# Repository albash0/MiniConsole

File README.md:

# MiniConsole

**A pocket game console built across embedded software, custom electronics, and physical design.**

*Built hardware: the earlier OLED handheld above and the color TFT handheld below. Photograph provided by the project author.*

An ESP32-S3 handheld with six buttons, OLED and color TFT versions, custom carrier PCBs, and a printable enclosure. The library combines arcade games, puzzles, an original traffic-planning implementation, adapted Doom support, and wireless play between two consoles.

A project by [albash0](https://github.com/albash0), a first-year ASEN and CTD student at CU Boulder.

[Engineering notes](docs/ENGINEERING.md) · [Hardware and case files](#hardware) · [Build instructions](docs/BUILD.md) · [Controls](docs/USER_GUIDE.md) · [Validation](VALIDATION.md)

## About the project

MiniConsole began with Snake and portrait Tetris on a 128 × 64 OLED. Extending it to a 240 × 135 color display introduced new memory, rendering, input, and mechanical-fit constraints. Wireless co-op added a second device whose state had to remain consistent with the first.

### From prototype to finished handheld

| Electronics iteration | Enclosure fit test | Assembled generations |
| --- | --- | --- |
|  |  |  |
| OLED protoboard prototype at the top; custom TFT PCB below. | A printed front shell brings together the display opening, button guides, fasteners, and handheld form. | Color TFT version in front; earlier OLED version behind. |

These build photographs show the progression from electronics integration to enclosure fitting and assembled devices. [Photo provenance and metadata handling](docs/media/photos/README.md).

### My project work

| Area | Work in this project | Source and evidence |
| --- | --- | --- |
| Firmware and interaction | Game launcher, six-button navigation, display profiles, themes, sound, and persistent checkpoints | [Main firmware](MiniConsole/MiniConsole.ino), [checkpoint implementation](MiniConsole/SuspendSave.h), [user guide](docs/USER_GUIDE.md) |
| Games and networking | Micro Motorways traffic simulation; Pocket Partners rooms and host-authoritative co-op; Block Battle Tetris mode | [Traffic model](MiniConsole/MotorwaysGame.h), [co-op implementation](MiniConsole/PartnersLink.h), [protocol tests](MiniConsole/tests/partners_test.cpp) |
| Hardware integration | OLED and TFT carrier-board designs, component/pin mapping, and fabrication outputs | [OLED carrier](MiniConsole/PCB/), [TFT carrier](MiniConsole/PCB-TFT114/) |
| Mechanical design | Screen/PCB fit, keyed button guides, and printable plain rear-shell choices | [STEP/STL parts and assembly constraints](hardware/case/) |
| Validation and tooling | Automated game/controller/rendering tests, firmware builds, and documented hardware bring-up | [Test runner](MiniConsole/tests/run_tests.sh), [validation report](VALIDATION.md) |

**Upstream work:** Doom support adapts DIABLITO, descended from RP2040 Doom and Chocolate Doom. The original game engine and assets have their own authors and licenses. My project integrates that engine with the S3, displays, controls, launcher, and saves. The complete adapted source is included under [DiablitoOLED](libraries/DiablitoOLED/); see [credits and licenses](THIRD_PARTY.md).

### Engineering decisions

- **Share game rules across displays:** keep common state and checkpoint formats while allowing native color rendering where it improves the interface.
- **Budget memory explicitly:** a single full-panel RGB565 buffer is 64,800 bytes; the TFT backend attempts PSRAM allocation first.
- **Use one authority for co-op physics:** the host owns the world state; clients send inputs and receive snapshots, with stalls and disconnects handled explicitly.
- **Treat fit as part of the system:** screen height, switch travel, retaining flanges, and battery clearance constrain the enclosure together.

[Read the decisions, source links, regression example, and next measurements →](docs/ENGINEERING.md)

### Status and validation

| Check | Evidence and limits |
| --- | --- |
| Automated tests | **30 host suites per display profile** pass with address/undefined-behavior sanitizers. [GitHub Actions](https://github.com/albash0/MiniConsole/actions). |
| Firmware | OLED and TFT profiles compiled for the public source release. |
| Physical devices | The [build photographs](#from-prototype-to-finished-handheld) show OLED/TFT assemblies and enclosure iteration. Development records document bring-up and nearby two-console co-op/battle testing. The source release itself did not include a new device flash or gameplay run. |
| CAD and fabrication | Editable KiCad designs, BOMs, fabrication files, and individual case parts are supplied. Physical assembly tolerances still need checking. |
| Open measurements | Battery runtime, defined wireless range, and repeatable frame-time comparisons remain to be measured. |

Host tests stub the Doom engine; their success does not establish Doom runtime behavior on hardware. [Validation details](VALIDATION.md).

### Timeline

Dates below come from dated validation notes and source/CAD records; early dates identify the earliest retained files, rather than a reconstructed Git history.

| Date | Milestone |
| --- | --- |
| 2026-10-12 | Earliest retained Snake and Tetris game sources. |
| 2026-10-13 | Breakout, Invaders and ten-level Sokoban; pause/resume checkpoints; DIABLITO-based Doom integration on the OLED console. |
| 2026-10-14 | Custom OLED and 1.14-inch TFT carrier-board design records. |
| 2026-10-16 | Going Out mode: persistent drink counter, configurable goal, and three party games. |
| 2026-10-29 | Color TFT firmware validated on the assembled console, including Doom. |
| 2026-10-30 | Native TFT game presentation and appearance work. |
| 2026-11-05 | Shorter case top selected after a physical test print. |
| 2026-11-09 | Piezo sound, Tetris music, themes, independent music/background controls, and keyed case refinements. |
| 2026-11-10–11 | Micro Motorways: traffic simulation, roads, bridges, express links, endless growth, diagonal roads and junction balancing. |
| 2026-11-12 | Wireless Tetris Block Battle and ten-room Pocket Partners co-op, tested on two TFT consoles. |
| 2026-11-17 | Public source preparation, portable build instructions and privacy review. |

## Games and controls

| Snake | Micro Motorways | Pocket Partners |
| --- | --- | --- |
|  |  |  |

*Host-rendered frames from the firmware's TFT renderer, separate from the physical build photographs above.*

The main library includes **Snake, Tetris, Breakout, Invaders, Sokoban, Doom, Micro Motorways, and Pocket Partners**. Tetris also has a two-console Block Battle mode. Pocket Partners has ten cooperative platform-puzzle rooms, and Sokoban has ten original puzzles.

The TFT version adds native menus, selected native game renderers, themes, and color. Checkpoints, settings, and high scores persist across restarts. Wireless modes use ESP-NOW without a router. Optional Going Out mode includes a drink counter and three party games; it is documented with the [full controls](docs/USER_GUIDE.md).

## Hardware

| Version or part | Files |
| --- | --- |
| OLED carrier V1.7 | [KiCad, Gerbers, BOM and board notes](MiniConsole/PCB/) |
| 1.14-inch ST7789 TFT carrier V1.3 | [KiCad, Gerbers, BOM and board notes](MiniConsole/PCB-TFT114/) |
| Keyed TFT enclosure | [Individual STEP/STL fronts, plain rears and buttons](hardware/case/) |

Both carriers use an ESP32-S3 SuperMini, six buttons, and an optional GPIO4 piezo through 220 Ω. Read the [TFT battery wiring correction](MiniConsole/PCB-TFT114/wiring/README.md) before assembly. The enclosure notes cover the thicker rear's battery-clearance constraint.

## Build and test

[The build guide](docs/BUILD.md) covers dependencies, OLED/TFT selection, first installation, and the separate Doom shareware-data download. Commands below run from the repository root:

```sh
python3 MiniConsole/tools/build_doom.py --display oled
python3 MiniConsole/tools/build_doom.py --display tft
sh MiniConsole/tests/run_tests.sh
DISPLAY_PROFILE=tft sh MiniConsole/tests/run_tests.sh
```

## License and credits

Original software, documentation and design files: **GPL-2.0-or-later**, except retained third-party notices. See [LICENSE](LICENSE) and [THIRD_PARTY.md](THIRD_PARTY.md). DIABLITO, RP2040 Doom, Chocolate Doom, id Software, Adafruit and KiCad contributors retain their credits and licenses. Doom game data is licensed separately.

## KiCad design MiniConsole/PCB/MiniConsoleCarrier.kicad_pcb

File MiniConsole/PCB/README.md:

# MiniConsole OLED carrier V1.7

Open `MiniConsoleCarrier.kicad_pro` in KiCad 10. The checked schematic, routed PCB, local symbols/footprints and unpacked manufacturing outputs are included. Use the native KiCad design as the authority; the EAGLE/Fusion interchange files may require copper-polygon regeneration and DRC after import.

The carrier is 70.1 × 30.1 mm with a 65.9 × 26.1 mm case mounting pattern. This revision adds five rear test pads and moves Left/Right inward 0.50 mm each. The expansion header is above Up. VCC and logic are 3.3 V. See `documentation/BOM.csv`, `manufacturing/`, and the retained geometry/check reports in `documentation/`.

Pin assignments and display setup are in [the user guide](../../docs/USER_GUIDE.md). The TFT carrier's firmware A/B mapping follows the physical assembled console and differs from older board labels. On the TFT board, read [the battery wiring correction](../PCB-TFT114/wiring/README.md) before wiring the battery. The PCB reference and copper pin numbers take precedence over conflicting silkscreen.

The original hardware records report no DRC/ERC violations with the configured rules. Those are historical CAD checks, not a new hardware test. Confirm module dimensions, polarity, clearances and the fabrication house's rules before manufacturing. Component models are nominal fit references; their original notices are under `3dmodels/`.

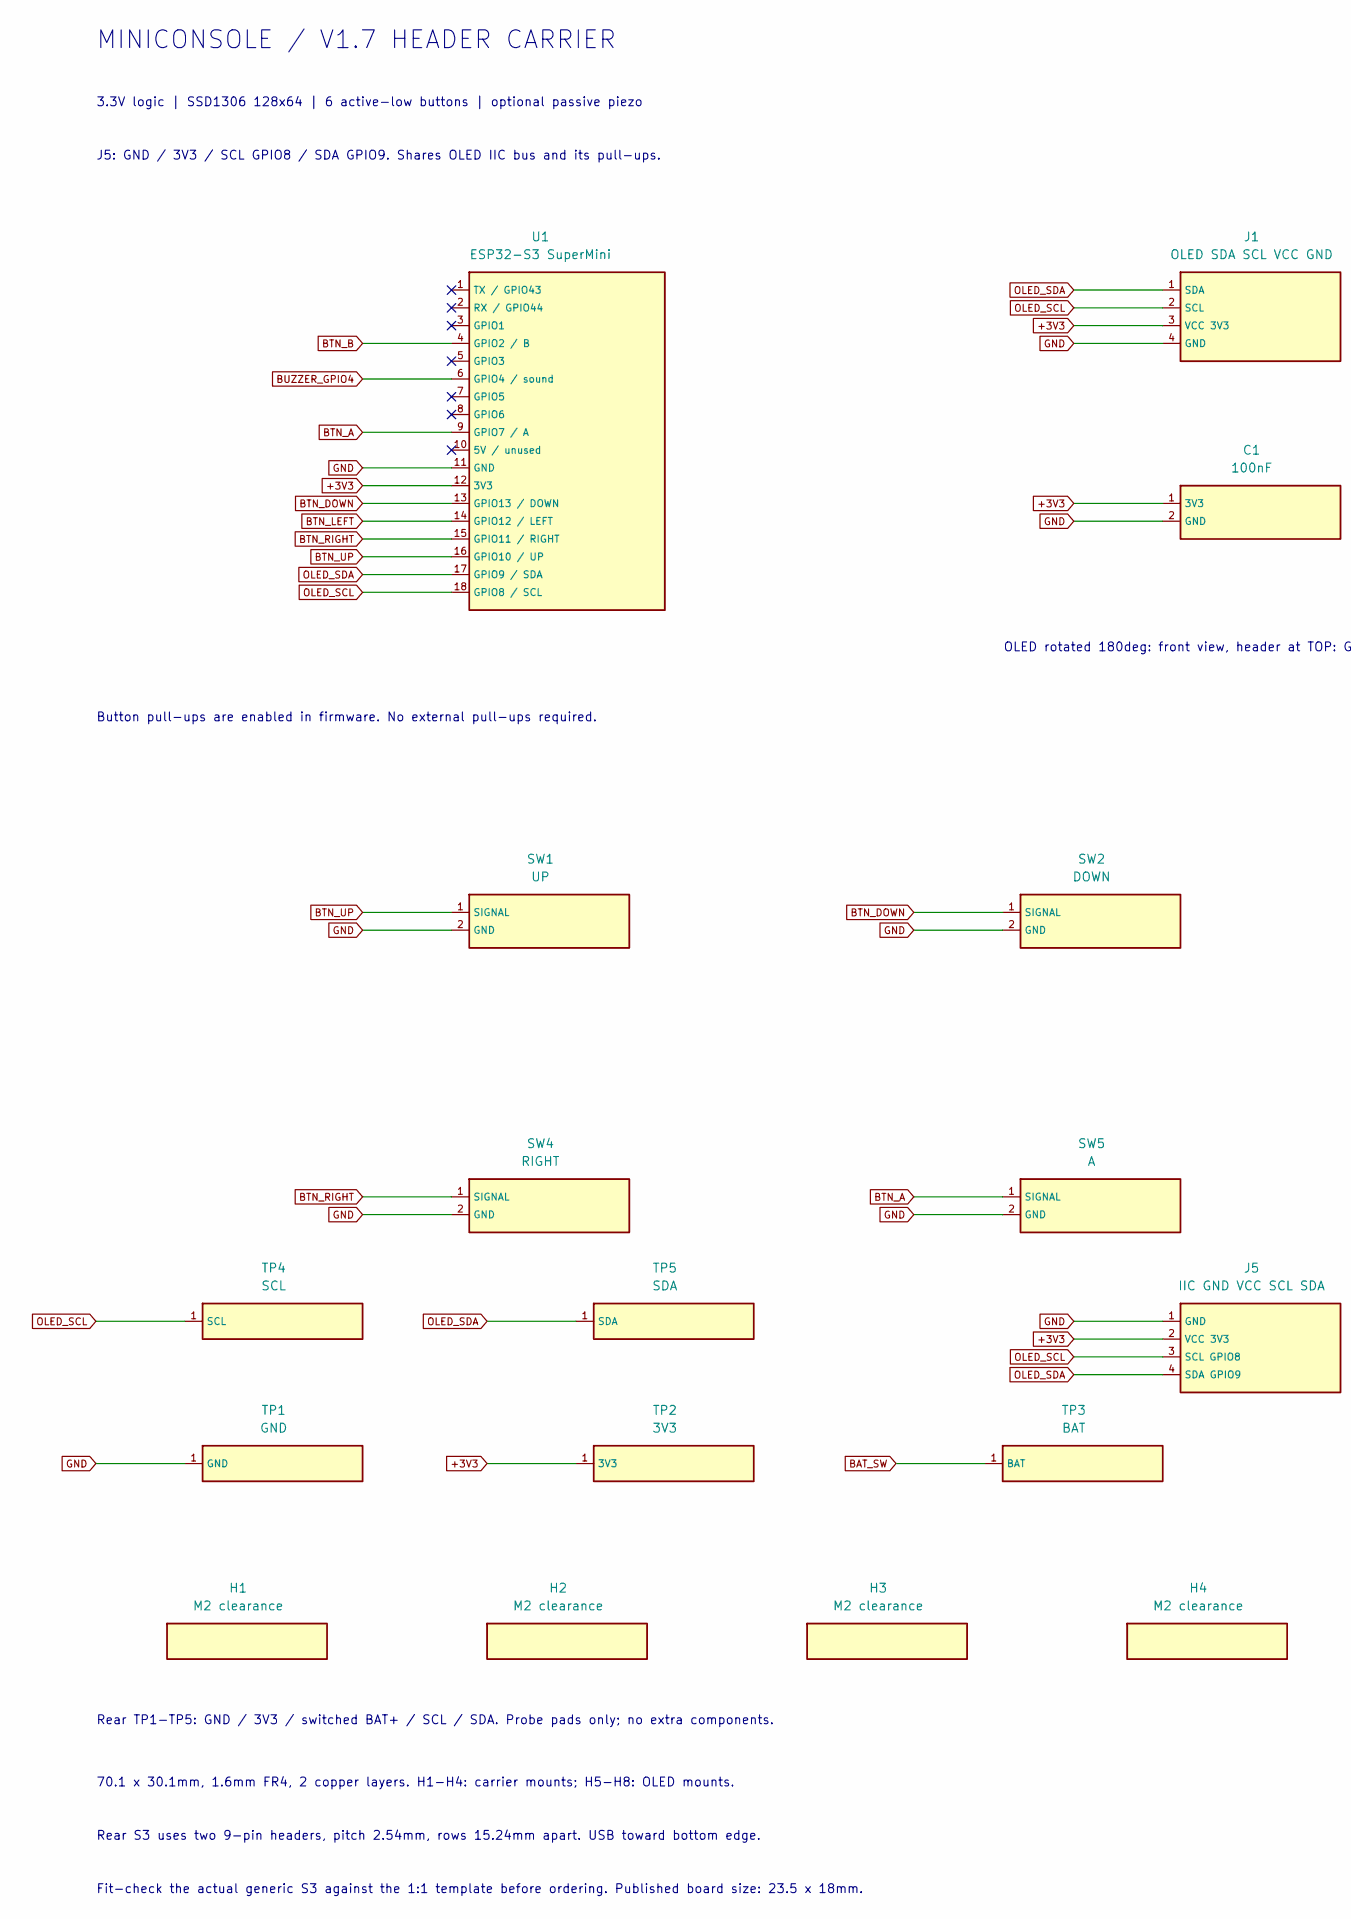
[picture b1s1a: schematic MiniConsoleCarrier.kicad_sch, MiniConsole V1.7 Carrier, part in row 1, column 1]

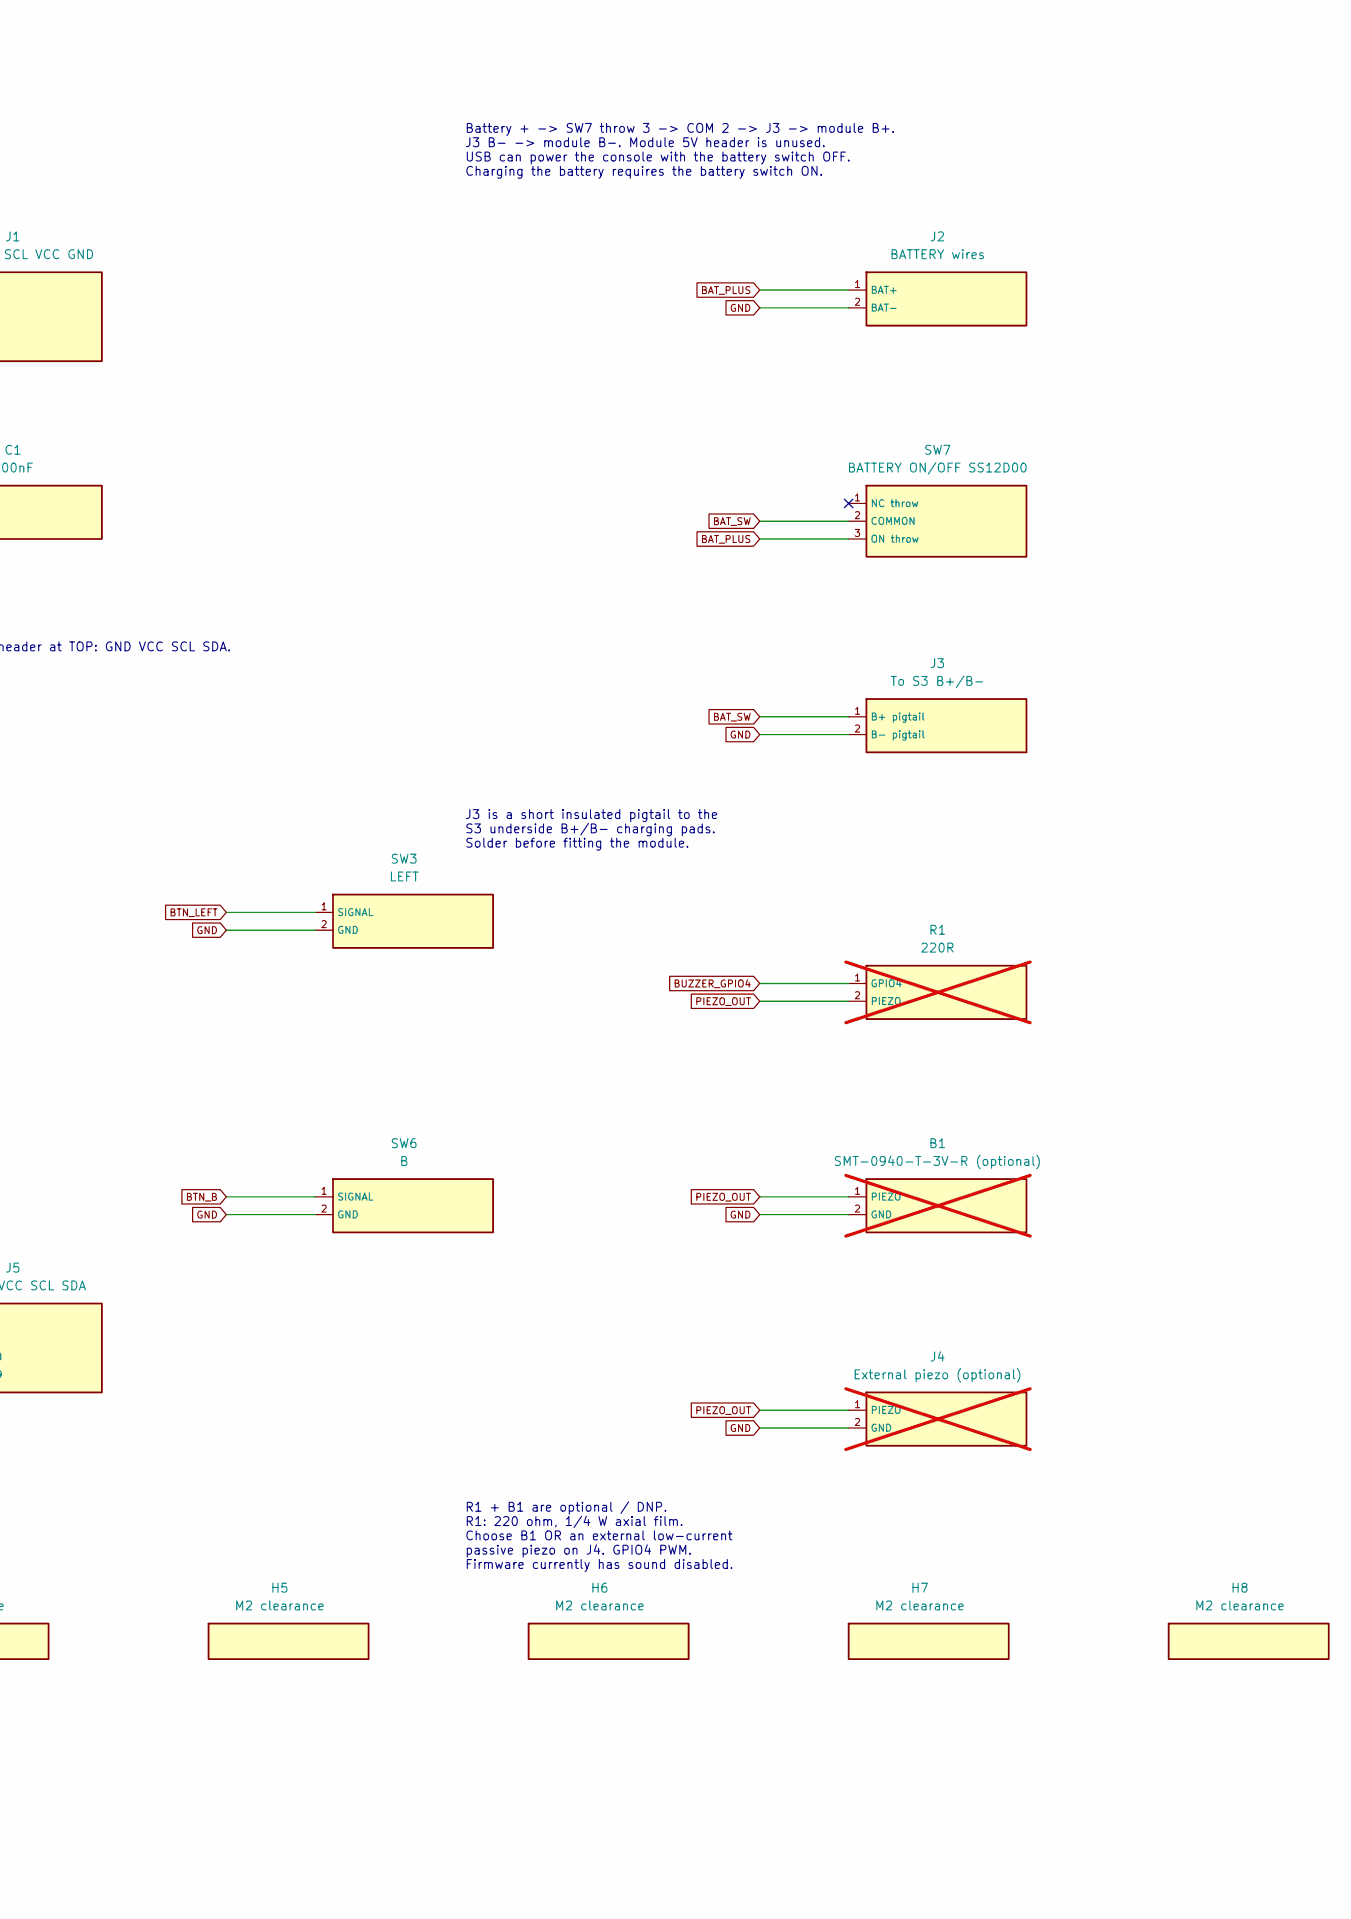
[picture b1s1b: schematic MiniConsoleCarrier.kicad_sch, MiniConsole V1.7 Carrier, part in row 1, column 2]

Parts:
B1: SMT-0940-T-3V-R (optional); Piezo_PUI_SMT0940_180; not fitted
C1: 100nF; C_0603_180
H1, H2, H3, H4, H5, H6, H7, H8: M2 clearance; Mount_M2
J1: OLED SDA SCL VCC GND; OLED_1x04
J2: BATTERY wires; Wire_2x_2.54_Reverse
J3: To S3 B+/B-; Wire_2x_2.54
J4: External piezo (optional); Wire_2x_2.54_Reverse; not fitted
J5: IIC GND VCC SCL SDA; IIC_1x04
R1: 220R; R_Axial_DIN0207_P7.62_220R; not fitted
SW1: UP; SW_6mm
SW2: DOWN; SW_6mm
SW3: LEFT; SW_6mm_90
SW4: RIGHT; SW_6mm_90
SW5: A; SW_6mm
SW6: B; SW_6mm
SW7: BATTERY ON/OFF SS12D00; SS12D00_LeftEdge_3pin
TP1: GND; TestPoint_D1p5_Rear
TP2: 3V3; TestPoint_D1p5_Rear
TP3: BAT; TestPoint_D1p5_Rear
TP4: SCL; TestPoint_D1p5_Rear
TP5: SDA; TestPoint_D1p5_Rear
U1: ESP32-S3 SuperMini; S3_Rear_USB_Down_2x09

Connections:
+3V3: C1.1 (3V3), J1.3 (VCC 3V3), J5.2 (VCC 3V3), TP2.1, U1.12 (3V3)
BAT_PLUS: J2.1 (BAT+), SW7.3 (ON throw)
BAT_SW: J3.1 (B+ pigtail), SW7.2 (COMMON), TP3.1
BTN_A: SW5.1 (SIGNAL), U1.9 (GPIO7 / A)
BTN_B: SW6.1 (SIGNAL), U1.4 (GPIO2 / B)
BTN_DOWN: SW2.1 (SIGNAL), U1.13 (GPIO13 / DOWN)
BTN_LEFT: SW3.1 (SIGNAL), U1.14 (GPIO12 / LEFT)
BTN_RIGHT: SW4.1 (SIGNAL), U1.15 (GPIO11 / RIGHT)
BTN_UP: SW1.1 (SIGNAL), U1.16 (GPIO10 / UP)
BUZZER_GPIO4: R1.1 (GPIO4), U1.6 (GPIO4 / sound)
GND: B1.2 (GND), C1.2 (GND), J1.4 (GND), J2.2 (BAT-), J3.2 (B- pigtail), J4.2 (GND), J5.1 (GND), SW1.2 (GND), SW2.2 (GND), SW3.2 (GND), SW4.2 (GND), SW5.2 (GND), SW6.2 (GND), TP1.1, U1.11 (GND)
OLED_SCL: J1.2 (SCL), J5.3 (SCL GPIO8), TP4.1, U1.18 (GPIO8 / SCL)
OLED_SDA: J1.1 (SDA), J5.4 (SDA GPIO9), TP5.1, U1.17 (GPIO9 / SDA)
PIEZO_OUT: B1.1 (PIEZO), J4.1 (PIEZO), R1.2 (PIEZO)

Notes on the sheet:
MINICONSOLE / V1.7 HEADER CARRIER
3.3V logic | SSD1306 128x64 | 6 active-low buttons | optional passive piezo
J5: GND / 3V3 / SCL GPIO8 / SDA GPIO9. Shares OLED IIC bus and its pull-ups.
Button pull-ups are enabled in firmware. No external pull-ups required.
OLED rotated 180deg: front view, header at TOP: GND VCC SCL SDA.
Battery + -> SW7 throw 3 -> COM 2 -> J3 -> module B+. J3 B- -> module B-. Module 5V header is unused. USB can power the console with the battery switch OFF. Charging the battery requires the battery switch ON.
J3 is a short insulated pigtail to the S3 underside B+/B- charging pads. Solder before fitting the module.
R1 + B1 are optional / DNP. R1: 220 ohm, 1/4 W axial film. Choose B1 OR an external low-current passive piezo on J4. GPIO4 PWM. Firmware currently has sound disabled.
Rear TP1-TP5: GND / 3V3 / switched BAT+ / SCL / SDA. Probe pads only; no extra components.
70.1 x 30.1mm, 1.6mm FR4, 2 copper layers. H1-H4: carrier mounts; H5-H8: OLED mounts.
Rear S3 uses two 9-pin headers, pitch 2.54mm, rows 15.24mm apart. USB toward bottom edge.
Fit-check the actual generic S3 against the 1:1 template before ordering. Published board size: 23.5 x 18mm.

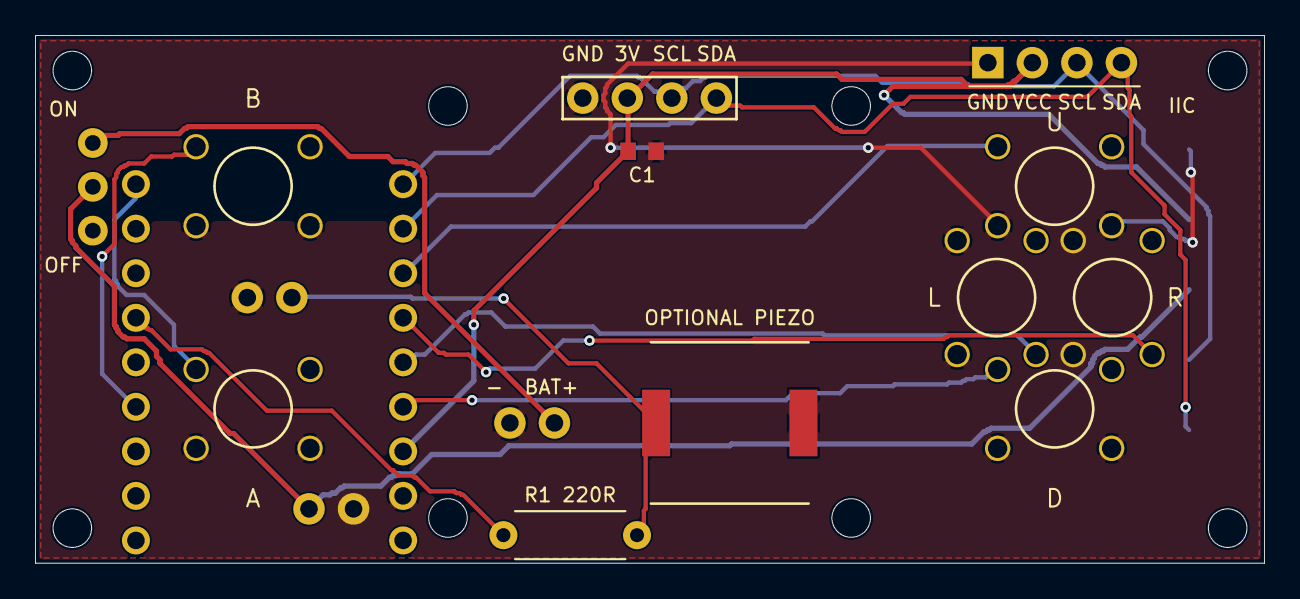
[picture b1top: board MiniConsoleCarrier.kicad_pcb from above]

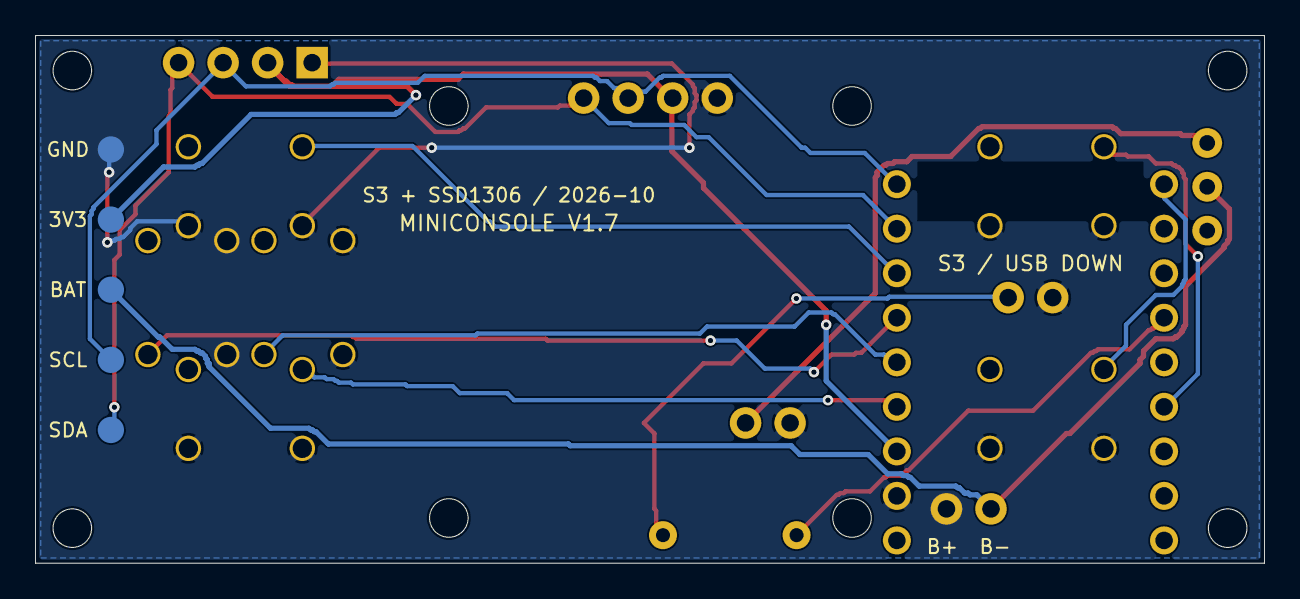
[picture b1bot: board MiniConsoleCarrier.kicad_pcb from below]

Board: 2 copper layers, 70.1 x 30.1 mm, 29 parts (6 on the bottom side), 14 nets.
